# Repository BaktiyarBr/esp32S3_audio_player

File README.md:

# aka_walkman — ESP32-S3 Hi-Fi Audio Player

A portable, battery-powered hi-fi audio player built around the **ESP32-S3** and the
**Cirrus Logic CS43131** DAC/headphone amplifier, designed in **KiCad** on a custom PCB.
Firmware is planned with ESP-IDF / ESP-ADF and custom drivers.

## Features

- Stereo hi-fi playback to a 3.5 mm headphone jack (CS43131 DAC + integrated headphone amp, 24.576 MHz audio clock)
- Audio sources: microSD card, Bluetooth, (optionally) USB
- Single-cell (1S) Li-ion battery with USB-C charging and a fuel gauge
- Push-button power on/off with a hard power cut when off (LTC2954 controller)
- UI: Nokia 5110 LCD, rotary encoder with push switch, 4× Cherry MX keys + 2 tactile buttons
- USB-C with ESD protection and a CP2102N USB-UART bridge for flashing / debug

## Key components

| Function | Part |
|---|---|
| MCU | ESP32-S3-WROOM-2 (N32R16V: 32 MB flash / 16 MB PSRAM) |
| DAC / headphone amp | CS43131-CNZR |
| 1.8 V logic level translation (I²S / I²C) | TXU0204, PCA9306 |
| Battery charger | BQ25185 |
| Buck-boost 3.3 V rail | TPS63020 |
| 1.8 V LDOs (codec rails) | 3× LP5907MFX-1.8 |
| Fuel gauge | MAX17048G |
| Power on/off controller | LTC2954-1 |
| USB-UART | CP2102N |
| USB ESD | USBLC6-2SC6 |
| Display | Nokia 5110 (PCD8544) |
| Encoder | SIQ-02FVS3 |

Full BOM with LCSC part numbers: [`production/bom.csv`](production/bom.csv).

## Repository layout

```
aka_walkman.kicad_pro      KiCad project
aka_walkman.kicad_sch      Root schematic (MCU, USB, UI, SD card)
power.kicad_sch            Power sheet (charger, buck-boost, LDOs, fuel gauge, on/off)
Audio.kicad_sch            Audio sheet (CS43131, clock, level shifters)
aka_walkman.kicad_pcb      PCB layout
aka_walkman.kicad_dru      Custom design rules
libs/                      Project symbol / footprint / 3D libraries (easyeda)
datasheets/                Key datasheets
production/                Fabrication outputs (gerbers zip, BOM, CPL, IPC netlist)
```

## Opening the project

1. Open `aka_walkman.kicad_pro` in KiCad 9 or newer.
2. Project-local libraries are referenced from `libs/` via `sym-lib-table` / `fp-lib-table`.

## Manufacturing

Fabrication files in `production/` are generated with the KiCad *Fabrication Toolkit* plugin
(settings in `fabrication-toolkit-options.json`) for JLCPCB-style ordering.

## Status

Work in progress — hardware design stage.

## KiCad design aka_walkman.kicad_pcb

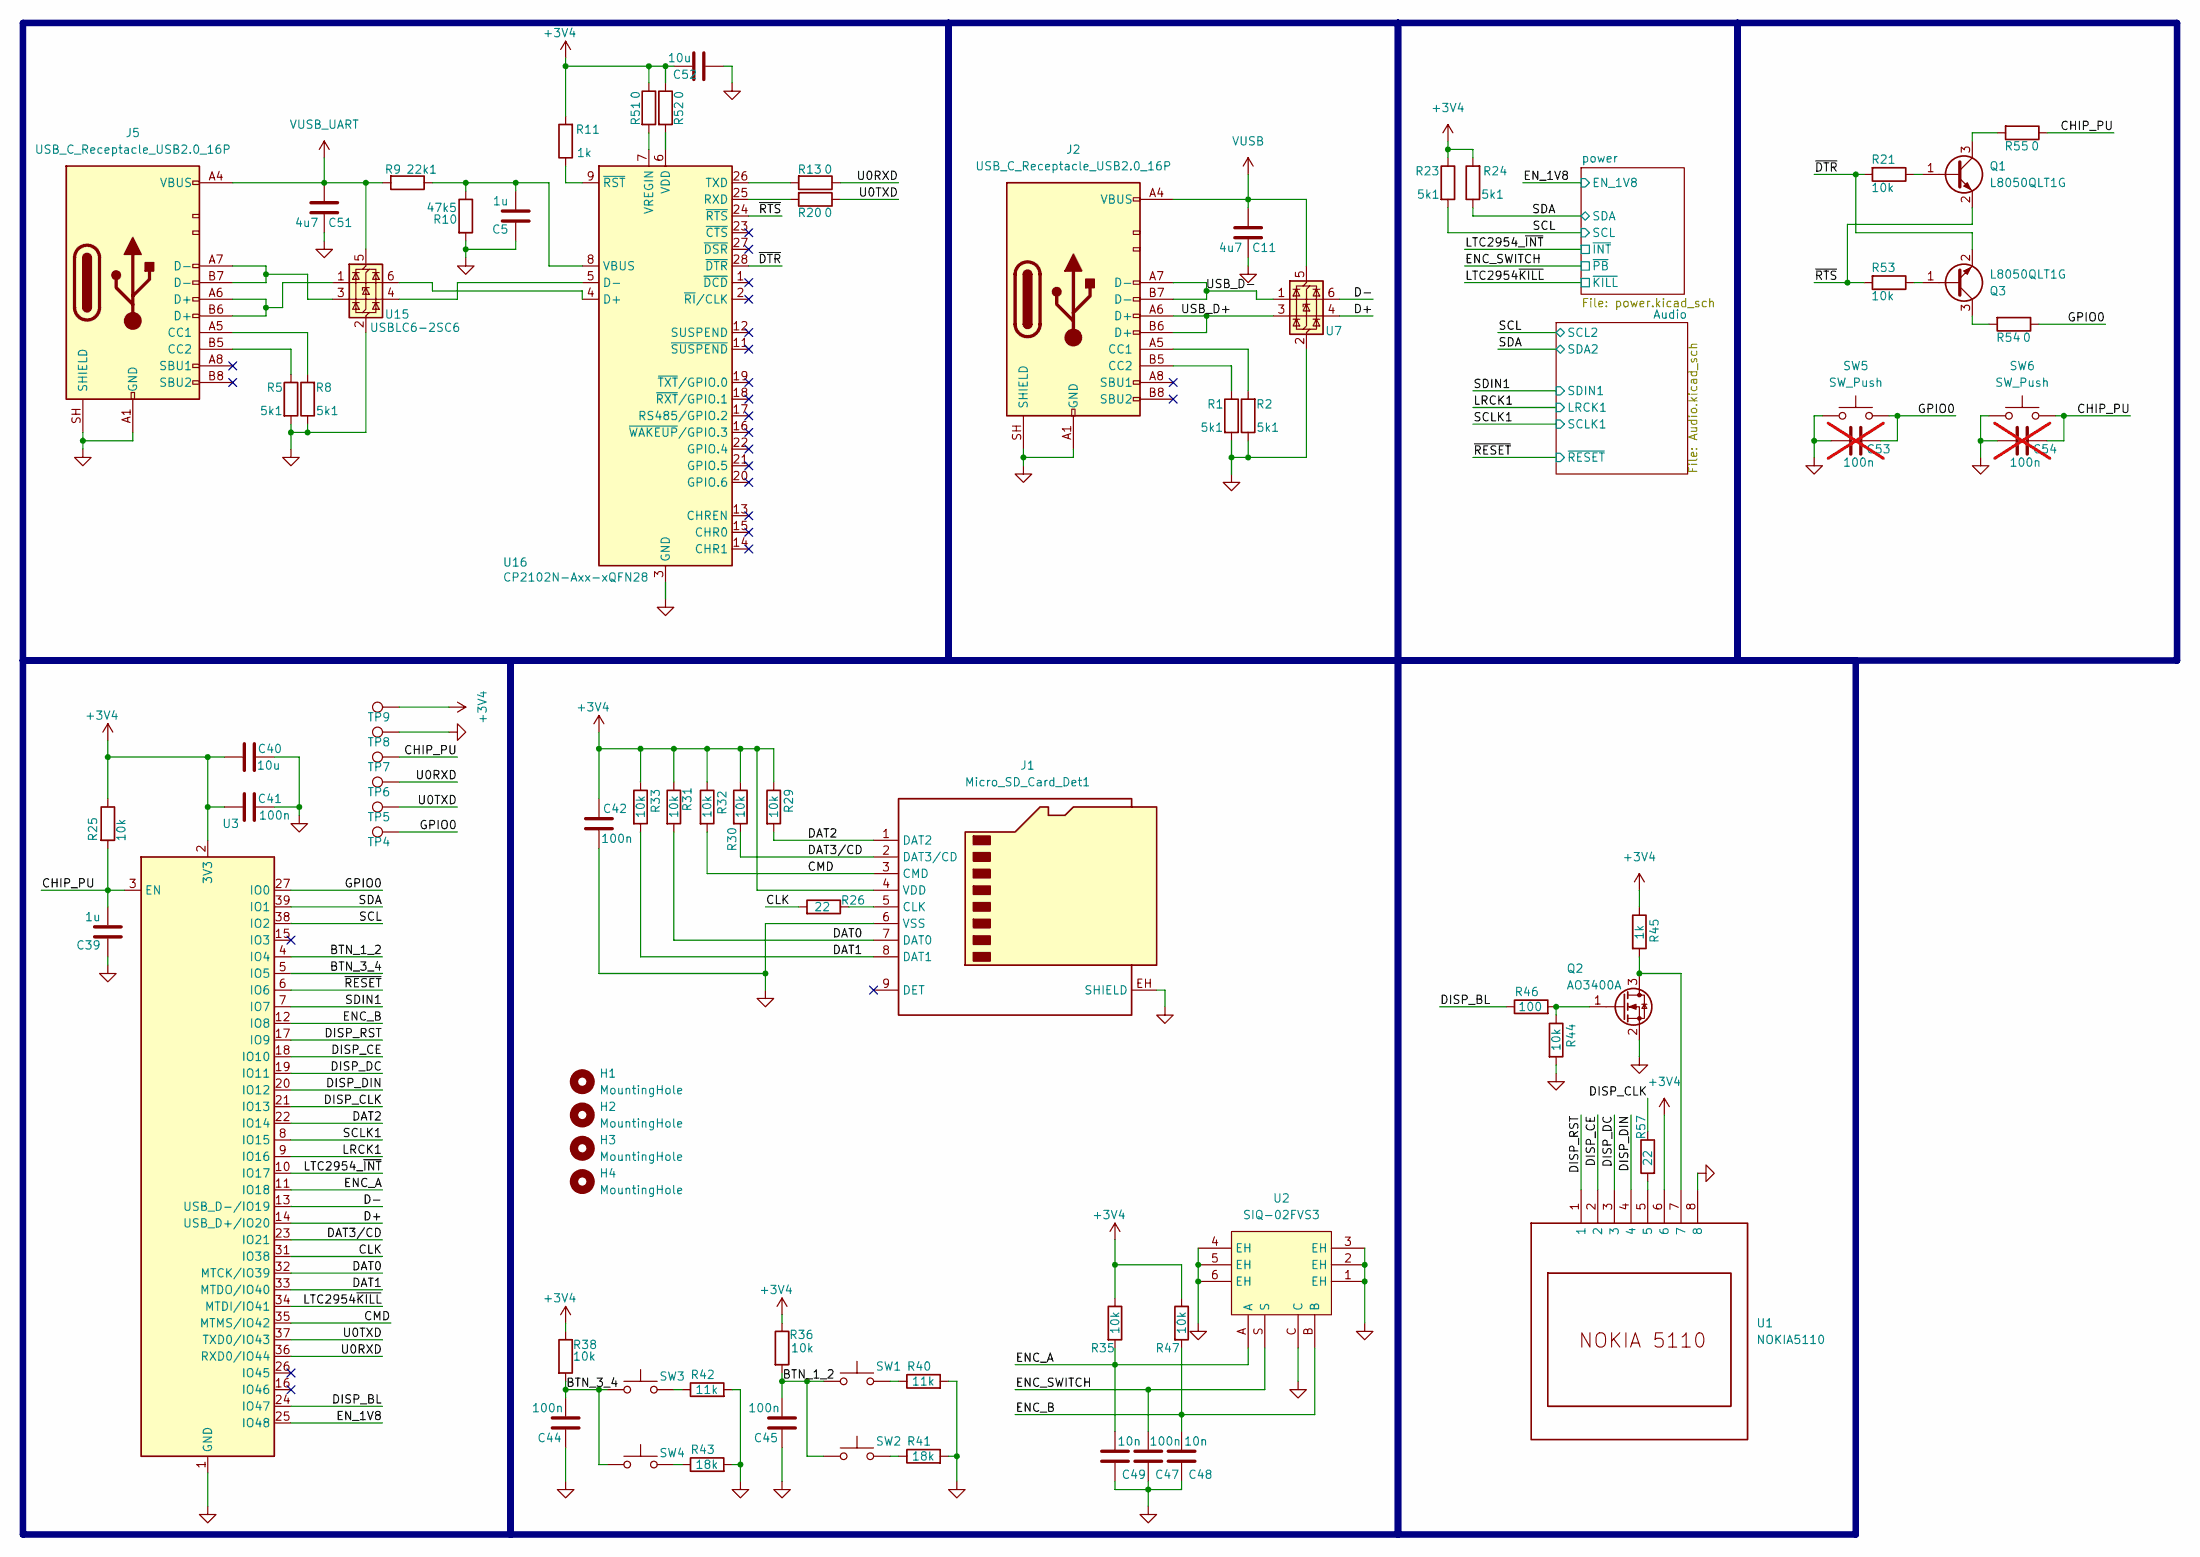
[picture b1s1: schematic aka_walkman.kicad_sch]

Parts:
C5, C39: 1u; C_0603_1608Metric; LCSC Part C15849
C11, C51: 4u7; C_0603_1608Metric; LCSC Part C1705
C40, C52: 10u; C_0603_1608Metric; LCSC Part C96446
C41, C42, C44, C45, C47: 100n; C_0603_1608Metric; LCSC Part C6119867
C48, C49: 10n; C_0603_1608Metric; LCSC Part C57112
C53, C54: 100n; C_0603_1608Metric; not fitted
H1, H2, H3, H4: MountingHole; MountingHole_2.7mm_M2.5
J1: Micro_SD_Card_Det1; SD-SMD_SD-47352-101; LCSC Part C293569
J2, J5: USB_C_Receptacle_USB2.0_16P; USB-TYPE-C-SMD_TYPE-C-16P-QTWT; LCSC Part C5187472
Q1, Q3: L8050QLT1G; SOT-23; LCSC Part C49581
Q2: AO3400A; SOT-23; LCSC Part C20917
R1, R2, R5, R8, R23, R24: 5k1; R_0603_1608Metric
R9: 22k1; R_0603_1608Metric
R10: 47k5; R_0603_1608Metric
R11, R45: 1k; R_0603_1608Metric
R13, R20, R51, R52, R54, R55: 0; R_0603_1608Metric
R21, R25, R29, R30, R31, R32, R33, R35, R36, R38, R44, R47, R53: 10k; R_0603_1608Metric
R26, R57: 22; R_0603_1608Metric; LCSC Part C26978
R40, R42: 11k; R_0603_1608Metric; LCSC Part C2906986
R41, R43: 18k; R_0603_1608Metric
R46: 100; R_0603_1608Metric; LCSC Part C22775
SW1, SW2, SW3, SW4: SW_Push; SW_Cherry_MX_PCB_1.00u
SW5, SW6: SW_Push; SW-SMD_L3.9-W3.0-P4.45
TP4, TP5, TP6, TP7, TP8, TP9: TestPoint; TestPoint_Pad_D1.5mm
U1: NOKIA5110; NOKIA5110-M01
U2: SIQ-02FVS3; SW-SMD_SIQ-02FVS3_1; MPN SIQ-02FVS3; LCSC Part C2925423
U3: ESP32-S3-WROOM-2; LCSC Part C42417293
U7, U15: USBLC6-2SC6; SOT-23-6; LCSC Part C7519
U16: CP2102N-Axx-xQFN28; QFN-28-1EP_5x5mm_P0.5mm_EP3.35x3.35mm; LCSC Part C964632

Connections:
+3V4: C40.1, C41.1, C42.1, C52.2, J1.4 (VDD), R11.2, R23.1, R24.2, R25.1, R29.1, R30.1, R31.1, R32.1, R33.1, R35.1, R36.1, R38.1, R45.1, R47.1, R51.1, R52.1, TP9.1 (1_1), U1.6, U3.2 (3V3); also elsewhere on the board
/BTN_1_2: C45.2, R36.2, SW1.1, SW2.1, U3.4 (IO4)
/BTN_3_4: C44.2, R38.2, SW3.1, SW4.1, U3.5 (IO5)
/CHIP_PU: C39.2, C54.1, R25.2, R55.1, SW6.2, TP7.1 (1_1), U3.3 (EN)
/CLK: R26.2, U3.31 (IO38)
/CMD: J1.3 (CMD), R32.2, U3.35 (MTMS/IO42)
/D+: U3.14 (USB_D+/IO20), U7.4 (I/O2)
/D-: U3.13 (USB_D-/IO19), U7.6 (I/O1)
/DAT0: J1.7 (DAT0), R31.2, U3.32 (MTCK/IO39)
/DAT1: J1.8 (DAT1), R33.2, U3.33 (MTDO/IO40)
/DAT2: J1.1 (DAT2), R29.2, U3.22 (IO14)
/DAT3/CD: J1.2 (DAT3/CD), R30.2, U3.23 (IO21)
/DISP_BL: R46.1, U3.24 (IO47)
/DISP_CE: U1.2, U3.18 (IO10)
/DISP_CLK: R57.1, U3.21 (IO13)
/DISP_DC: U1.3, U3.19 (IO11)
/DISP_DIN: U1.4, U3.20 (IO12)
/DISP_RST: U1.1, U3.17 (IO9)
/ENC_A: C49.2, R35.2, U2.A, U3.11 (IO18)
/ENC_B: C48.2, R47.2, U2.B, U3.12 (IO8)
/ENC_SWITCH: C47.2, U2.S; also elsewhere on the board
/EN_1V8: U3.25 (IO48); also elsewhere on the board
/GPIO0: C53.1, R54.1, SW5.2, TP4.1 (1_1), U3.27 (IO0)
/LRCK1: U3.9 (IO16); also elsewhere on the board
/LTC2954_~INT: U3.10 (IO17); also elsewhere on the board
/LTC2954~KILL: U3.34 (MTDI/IO41); also elsewhere on the board
/SCL: R23.2, U3.38 (IO2); also elsewhere on the board
/SCLK1: U3.8 (IO15); also elsewhere on the board
/SDA: R24.1, U3.39 (IO1); also elsewhere on the board
/SDIN1: U3.7 (IO7); also elsewhere on the board
/U0RXD: R13.1, TP6.1 (1_1), U3.36 (RXD0/IO44)
/U0TXD: R20.1, TP5.1 (1_1), U3.37 (TXD0/IO43)
/USB_D+: J2.A6 (D+), J2.B6 (D+), U7.3 (I/O2)
/USB_D-: J2.A7 (D-), J2.B7 (D-), U7.1 (I/O1)
/~DTR: Q3.2 (E), R21.2, U16.28 (~DTR)
/~RESET: U3.6 (IO6); also elsewhere on the board
/~RTS: Q1.2 (E), R53.2, U16.24 (~RTS)
GND: C5.1, C11.2, C39.1, C40.2, C41.2, C42.2, C44.1, C45.1, C47.1, C48.1, C49.1, C51.2, C52.1, C53.2, C54.2, J1.6 (VSS), J1.EH (SHIELD), J2.A1 (GND), J2.A12 (GND), J2.B1 (GND), J2.B12 (GND), J2.SH (SHIELD), J5.A1 (GND), J5.A12 (GND), J5.B1 (GND), J5.B12 (GND), J5.SH (SHIELD), Q2.2 (S), R1.2, R2.1, R5.2, R8.1, R10.2, R40.2, R41.2, R42.2, R43.2, R44.2, SW5.1, SW6.1, TP8.1 (1_1), U1.8, U2.1 (EH), U2.2 (EH), U2.3 (EH), U2.4 (EH), U2.5 (EH), U2.6 (EH), U2.C, U3.1 (GND), U3.40 (GND), U3.41 (GND), U7.2 (GND), U15.2 (GND), U16.3 (GND), U16.29 (GND); also elsewhere on the board
unnamed: J1.5 (CLK), R26.1
unnamed: J2.A5 (CC1), R2.2
unnamed: J2.B5 (CC2), R1.1
unnamed: J5.A5 (CC1), R8.2
unnamed: J5.B5 (CC2), R5.1
unnamed: J5.A6 (D+), J5.B6 (D+), U15.1 (I/O1)
unnamed: J5.A7 (D-), J5.B7 (D-), U15.3 (I/O2)
unnamed: Q1.1 (B), R21.1
unnamed: Q1.3 (C), R55.2
unnamed: Q2.3 (D), R45.2, U1.7
unnamed: Q2.1 (G), R44.1, R46.2
unnamed: Q3.1 (B), R53.1
unnamed: Q3.3 (C), R54.2
unnamed: R40.1, SW1.2
unnamed: R41.1, SW2.2
unnamed: R42.1, SW3.2
unnamed: R43.1, SW4.2
unnamed: R57.2, U1.5
unnamed: U15.6 (I/O1), U16.4 (D+)
unnamed: U15.4 (I/O2), U16.5 (D-)
unnamed: R20.2, U16.25 (RXD)
unnamed: R13.2, U16.26 (TXD)
unnamed: C5.2, R9.1, R10.1, U16.8 (VBUS)
unnamed: R52.2, U16.6 (VDD)
unnamed: R51.2, U16.7 (VREGIN)
unnamed: R11.1, U16.9 (~RST)
VUSB: C11.1, J2.A4 (VBUS), J2.A9 (VBUS), J2.B4 (VBUS), J2.B9 (VBUS), U7.5 (VBUS); also elsewhere on the board
VUSB_UART: C51.1, J5.A4 (VBUS), J5.A9 (VBUS), J5.B4 (VBUS), J5.B9 (VBUS), R9.2, U15.5 (VBUS); also elsewhere on the board

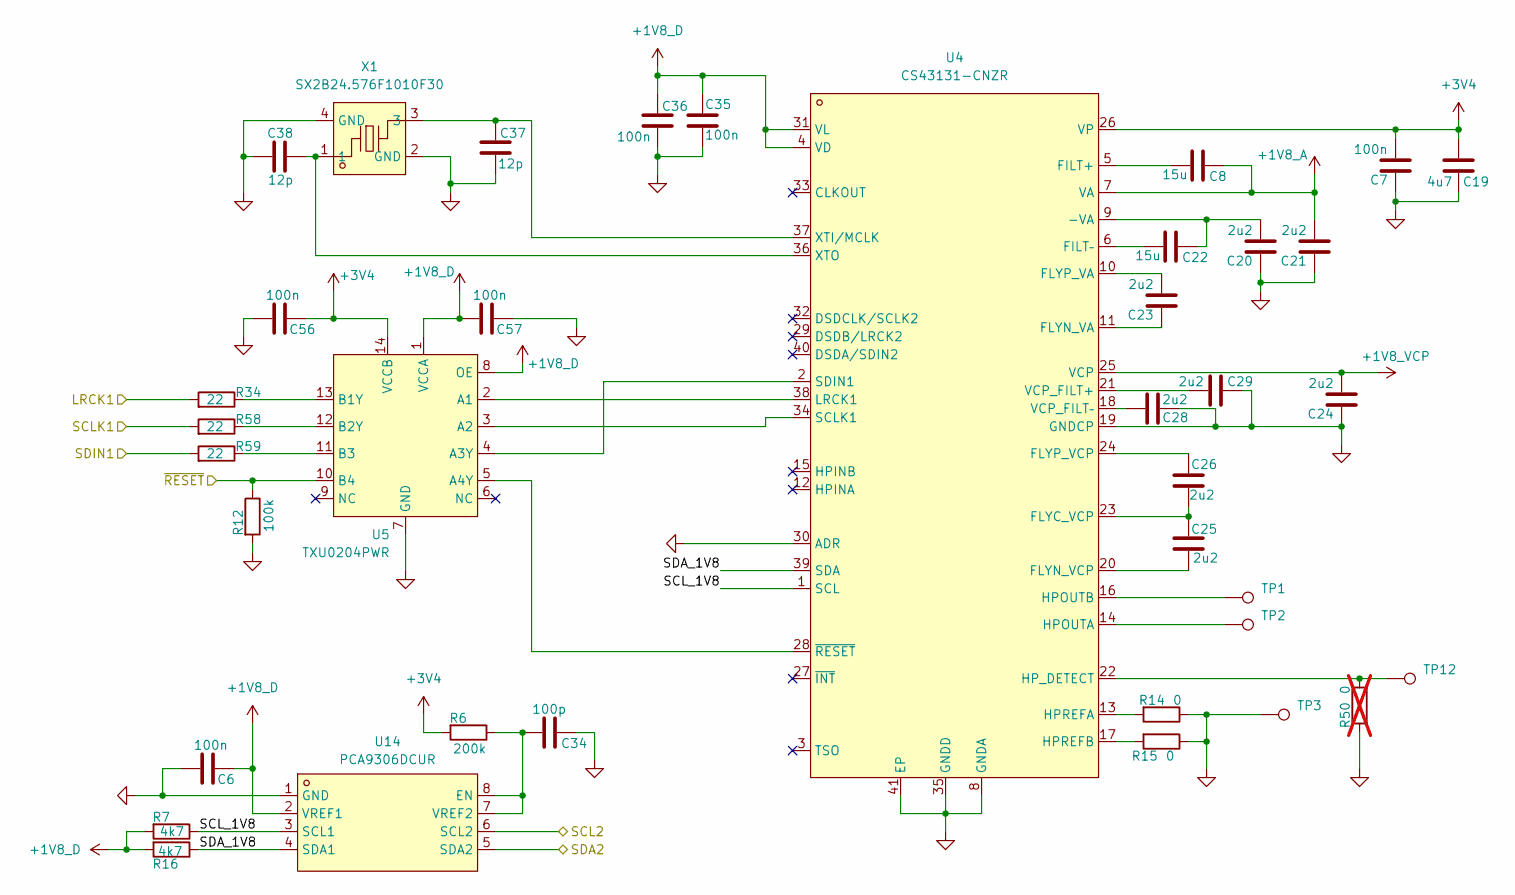
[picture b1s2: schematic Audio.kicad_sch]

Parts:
C6, C7, C35, C36, C56, C57: 100n; C_0603_1608Metric; LCSC Part C6119867
C8, C22: 15u; C_0805_2012Metric; LCSC Part C5367448
C19: 4u7; C_0603_1608Metric; LCSC Part C1705
C20, C21, C23, C24, C25, C26, C28, C29: 2u2; C_0603_1608Metric; LCSC Part C57895
C34: 100p; C_0603_1608Metric; LCSC Part C14665
C37, C38: 12p; C_0402_1005Metric; LCSC Part C26406
R6: 200k; R_0402_1005Metric; LCSC Part C2906866
R7, R16: 4k7; R_0603_1608Metric
R12: 100k; R_0603_1608Metric; LCSC Part C95177
R14, R15: 0; R_0603_1608Metric
R34, R58, R59: 22; R_0603_1608Metric; LCSC Part C26978
R50: 0; R_0603_1608Metric; not fitted
TP1, TP2, TP3, TP12: TestPoint; TestPoint_Pad_1.0x1.0mm
U4: CS43131-CNZR; TQFN-40_L5.0-W5.0-P0.40-TL-EP3.5; MPN CS43131-CNZR; LCSC Part C965907
U5: TXU0204PWR; TSSOP-14_L5.0-W4.4-P0.65-LS6.4-BL; MPN TXU0204PWR; LCSC Part C4363888
U14: PCA9306DCUR; SSOP-8_L2.0-W2.3-P0.50-LS3.1-BR; MPN PCA9306DCUR; LCSC Part C33196
X1: SX2B24.576F1010F30; CRYSTAL-SMD_4P-L2.5-W2.0-BL; MPN SX2B24.576F1010F30; LCSC Part C7301978

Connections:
+1V8_A: C8.1, C21.2, U4.7 (VA); also elsewhere on the board
+1V8_D: C6.1, C35.1, C36.1, C57.2, R7.2, R16.2, U4.4 (VD), U4.31 (VL), U5.1 (VCCA), U5.8 (OE), U14.2 (VREF1); also elsewhere on the board
+1V8_VCP: C24.2, U4.25 (VCP); also elsewhere on the board
+3V4: C7.2, C19.1, C56.1, R6.2, U4.26 (VP), U5.14 (VCCB); also elsewhere on the board
/Audio/SCL_1V8: R7.1, U4.1 (SCL), U14.3 (SCL1)
/Audio/SDA_1V8: R16.1, U4.39 (SDA), U14.4 (SDA1)
/LRCK1: R34.2; also elsewhere on the board
/SCL: U14.6 (SCL2); also elsewhere on the board
/SCLK1: R58.2; also elsewhere on the board
/SDA: U14.5 (SDA2); also elsewhere on the board
/SDIN1: R59.2; also elsewhere on the board
/~RESET: R12.1, U5.10 (B4); also elsewhere on the board
GND: C6.2, C7.1, C19.2, C20.1, C21.1, C24.1, C28.1, C29.1, C34.1, C35.2, C36.2, C37.2, C38.1, C56.2, C57.1, R12.2, R14.1, R15.1, R50.2, TP3.1 (1_1), U4.8 (GNDA), U4.19 (GNDCP), U4.30 (ADR), U4.35 (GNDD), U4.41 (EP), U5.7 (GND), U14.1 (GND), X1.2 (GND), X1.4 (GND); also elsewhere on the board
unnamed: C20.2, C22.1, U4.9 (-VA)
unnamed: C8.2, U4.5 (FILT+)
unnamed: C22.2, U4.6 (FILT–)
unnamed: C25.1, C26.2, U4.23 (FLYC_VCP)
unnamed: C23.1, U4.11 (FLYN_VA)
unnamed: C25.2, U4.20 (FLYN_VCP)
unnamed: C23.2, U4.10 (FLYP_VA)
unnamed: C26.1, U4.24 (FLYP_VCP)
unnamed: TP2.1 (1_1), U4.14 (HPOUTA)
unnamed: TP1.1 (1_1), U4.16 (HPOUTB)
unnamed: R14.2, U4.13 (HPREFA)
unnamed: R15.2, U4.17 (HPREFB)
unnamed: R50.1, TP12.1 (1_1), U4.22 (HP_DETECT)
unnamed: U4.38 (LRCK1), U5.2 (A1)
unnamed: U4.34 (SCLK1), U5.3 (A2)
unnamed: U4.2 (SDIN1), U5.4 (A3Y)
unnamed: C29.2, U4.21 (VCP_FILT+)
unnamed: C28.2, U4.18 (VCP_FILT–)
unnamed: C37.1, U4.37 (XTI/MCLK), X1.3
unnamed: C38.2, U4.36 (XTO), X1.1
unnamed: U4.28 (~RESET), U5.5 (A4Y)
unnamed: R34.1, U5.13 (B1Y)
unnamed: R58.1, U5.12 (B2Y)
unnamed: R59.1, U5.11 (B3)
unnamed: C34.2, R6.1, U14.7 (VREF2), U14.8 (EN)

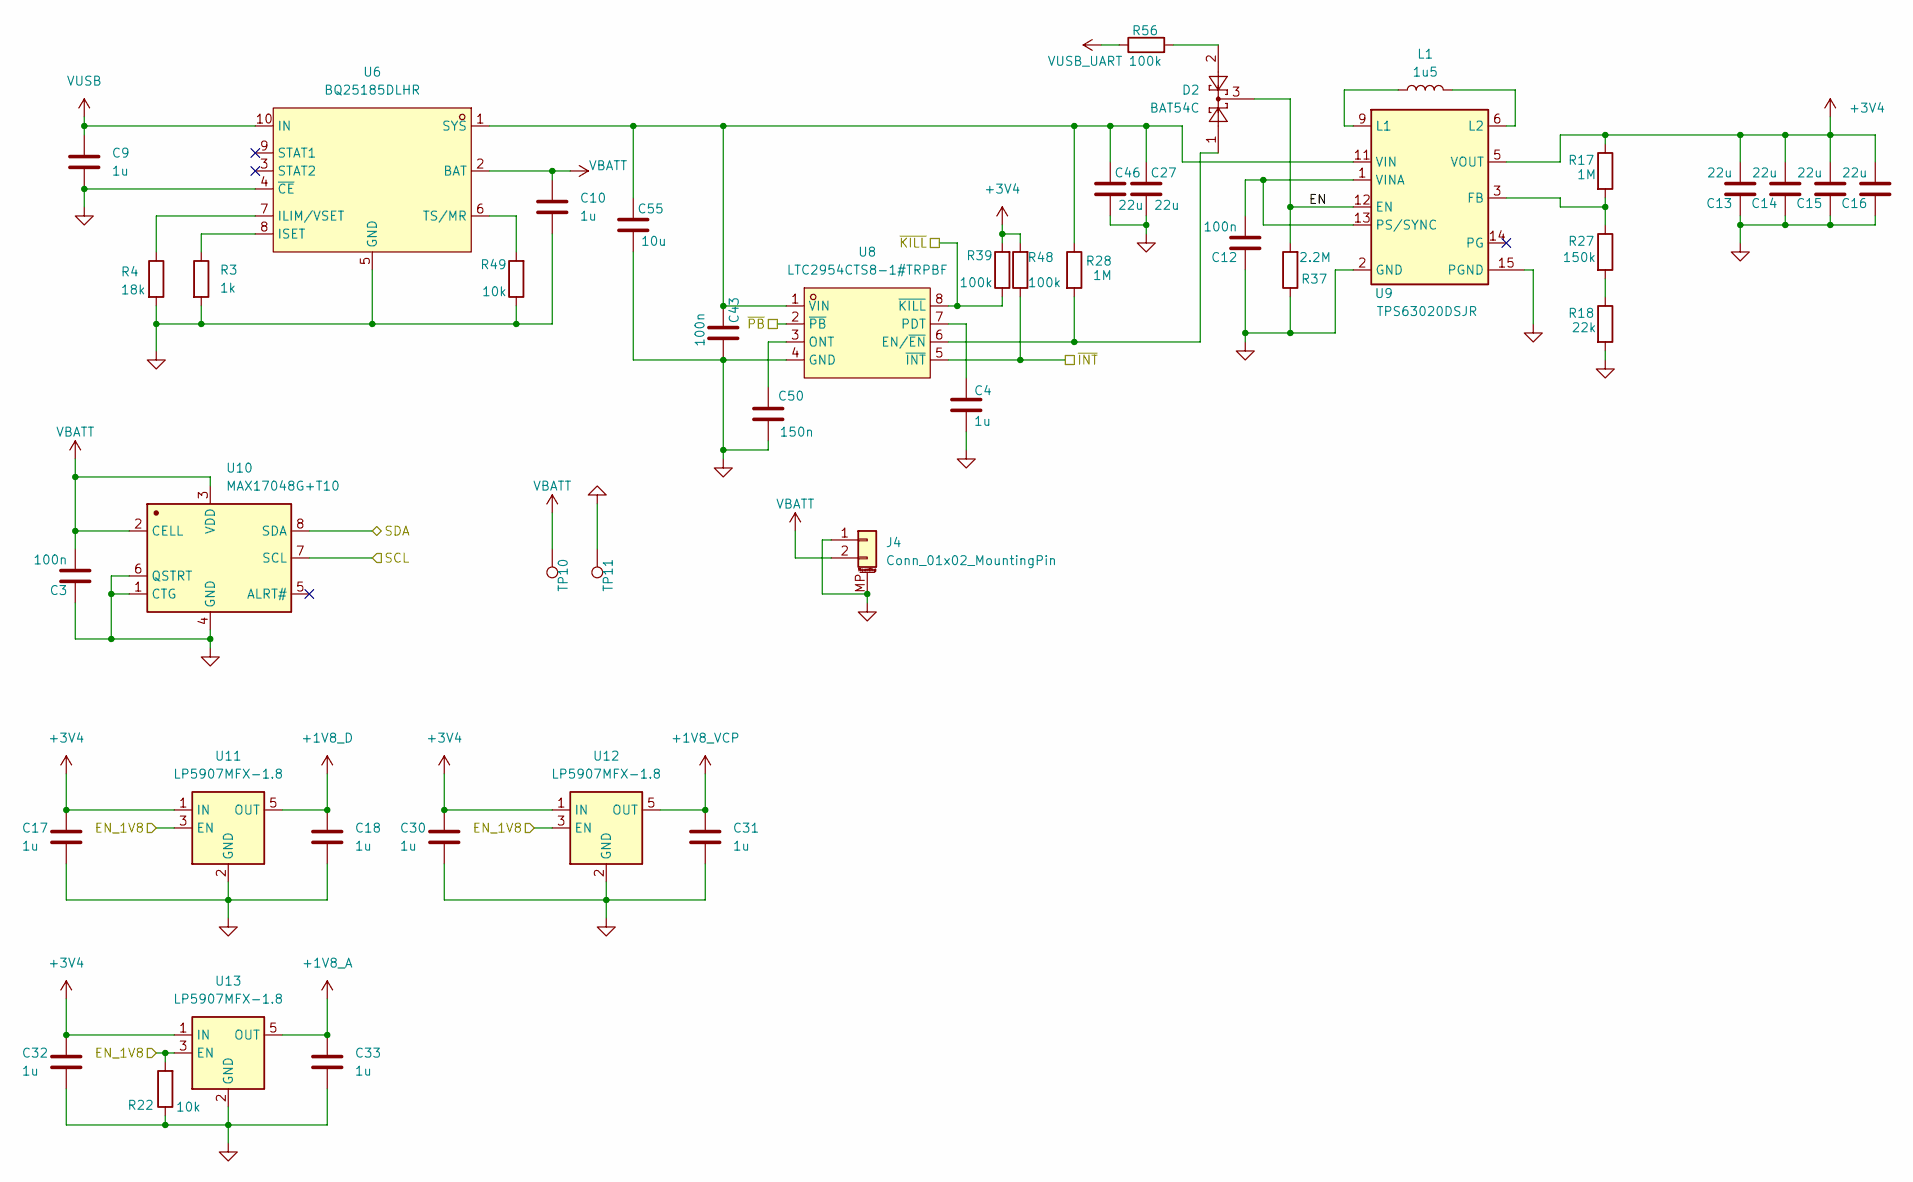
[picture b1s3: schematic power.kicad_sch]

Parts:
C3, C12, C43: 100n; C_0603_1608Metric; LCSC Part C6119867
C4: 1u; C_0603_1608Metric; LCSC Part C15849
C9, C10, C17, C18, C30, C31, C32, C33: 1u; C_0603_1608Metric; Part-DB Footprint 0603; LCSC Part C15849
C13, C14, C15, C16, C27, C46: 22u; C_0805_2012Metric; LCSC Part C45783
C50: 150n; C_0603_1608Metric; Part-DB Footprint 0603; LCSC Part C513735
C55: 10u; C_0603_1608Metric; LCSC Part C96446
D2: BAT54C; SOT-23; LCSC Part C916424
J4: Conn_01x02_MountingPin; JST_GH_SM02B-GHS-TB_1x02-1MP_P1.25mm_Horizontal
L1: 1u5; L_Bourns-SRN4018; LCSC Part C5349662
R3: 1k; R_0603_1608Metric
R4: 18k; R_0603_1608Metric
R17, R28: 1M; R_0603_1608Metric
R18: 22k; R_0603_1608Metric
R22, R49: 10k; R_0603_1608Metric
R27: 150k; R_0603_1608Metric
R37: 2.2M; R_0603_1608Metric; LCSC Part C2933170
R39, R48, R56: 100k; R_0603_1608Metric; LCSC Part C95177
TP10, TP11: TestPoint; TestPoint_Pad_D1.5mm
U6: BQ25185DLHR; WSON-10_L2.2-W2.0-P0.40-BL-EP_TI_DLH0010A; MPN BQ25185DLHR; LCSC Part C19725033
U8: LTC2954CTS8-1#TRPBF; TSOT-23-8_L2.9-W1.6-P0.65-LS2.8-BL; MPN LTC2954CTS8-1#TRPBF; LCSC Part C683782
U9: TPS63020DSJR; VSON-14_L4.0-W3.0-P0.50-BL-EP_TI_DSJ; Manufacturer Part TPS63020DSJR; LCSC Part C15483
U10: MAX17048G+T10; TDFN-8_L2.0-W2.0-P0.50-BL-EP1.2; Manufacturer Part MAX17048G+T10; LCSC Part C2682616
U11, U12, U13: LP5907MFX-1.8; SOT-23-5; LCSC Part C92498

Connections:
+1V8_A: C33.1, U13.5 (OUT); also elsewhere on the board
+1V8_D: C18.1, U11.5 (OUT); also elsewhere on the board
+1V8_VCP: C31.1, U12.5 (OUT); also elsewhere on the board
+3V4: C13.2, C14.2, C15.2, C16.2, C17.1, C30.1, C32.1, R17.1, R39.2, R48.2, U9.4 (VOUT), U9.5 (VOUT), U11.1 (IN), U12.1 (IN), U13.1 (IN); also elsewhere on the board
/ENC_SWITCH: U8.2 (~PB); also elsewhere on the board
/EN_1V8: R22.2, U11.3 (EN), U12.3 (EN), U13.3 (EN); also elsewhere on the board
/LTC2954_~INT: R48.1, U8.5 (~INT); also elsewhere on the board
/LTC2954~KILL: R39.1, U8.8 (~KILL); also elsewhere on the board
/SCL: U10.7 (SCL); also elsewhere on the board
/SDA: U10.8 (SDA); also elsewhere on the board
/power/EN: D2.3, R37.2, U9.12 (EN)
GND: C3.1, C4.2, C9.2, C10.2, C12.1, C13.1, C14.1, C15.1, C16.1, C17.2, C18.2, C27.2, C30.2, C31.2, C32.2, C33.2, C43.2, C46.2, C50.2, C55.2, J4.1, J4.MP (MountPin), R3.2, R4.2, R18.2, R22.1, R37.1, R49.1, TP11.1 (1_1), U6.4 (~CE), U6.5 (GND), U6.11 (EP), U8.4 (GND), U9.2 (GND), U9.15 (PGND), U10.1 (CTG), U10.4 (GND), U10.6 (QSTRT), U10.9 (EP), U11.2 (GND), U12.2 (GND), U13.2 (GND); also elsewhere on the board
unnamed: D2.2, R56.2
unnamed: L1.1, U9.8 (L1), U9.9 (L1)
unnamed: L1.2, U9.6 (L2), U9.7 (L2)
unnamed: R18.1, R27.2
unnamed: R4.1, U6.7 (ILIM/VSET)
unnamed: R3.1, U6.8 (ISET)
unnamed: C27.1, C43.1, C46.1, C55.1, R28.1, U6.1 (SYS), U8.1 (VIN), U9.10 (VIN), U9.11 (VIN)
unnamed: R49.2, U6.6 (TS/MR)
unnamed: D2.1, R28.2, U8.6 (EN/~EN)
unnamed: C50.1, U8.3 (ONT)
unnamed: C4.1, U8.7 (PDT)
unnamed: R17.2, R27.1, U9.3 (FB)
unnamed: C12.2, U9.1 (VINA), U9.13 (PS/SYNC)
VBATT: C3.2, C10.1, J4.2, TP10.1 (1_1), U6.2 (BAT), U10.2 (CELL), U10.3 (VDD)
VUSB: C9.1, U6.10 (IN); also elsewhere on the board
VUSB_UART: R56.1; also elsewhere on the board

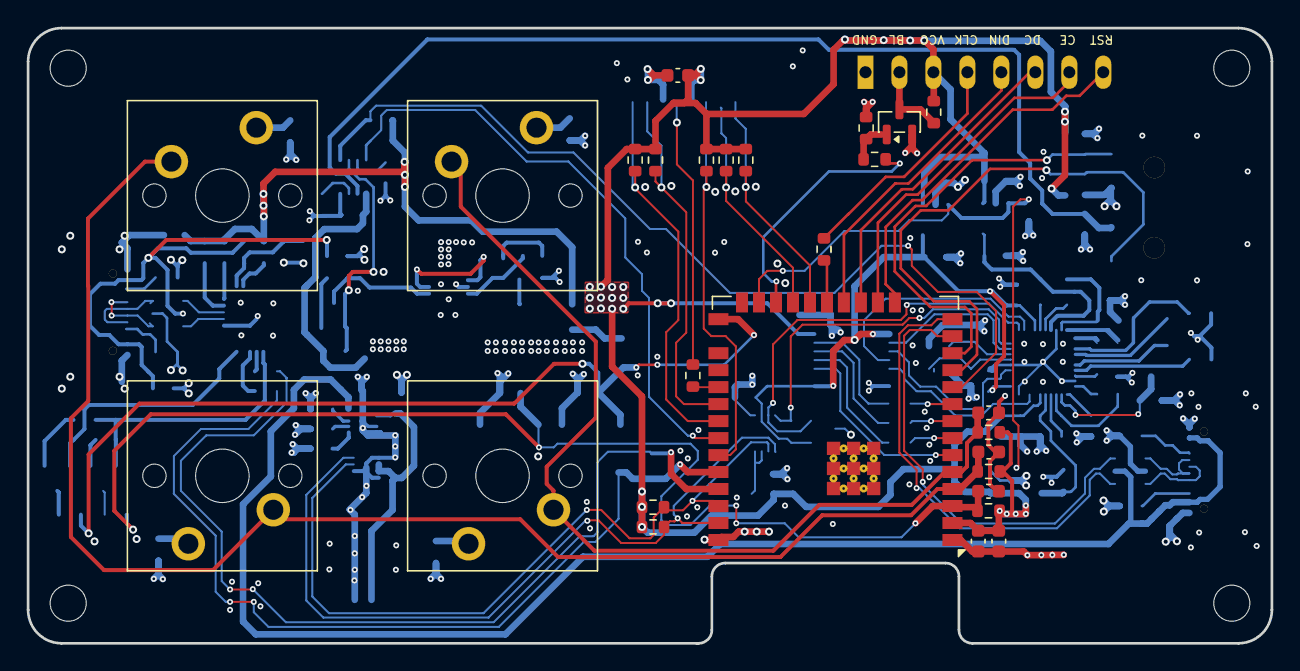
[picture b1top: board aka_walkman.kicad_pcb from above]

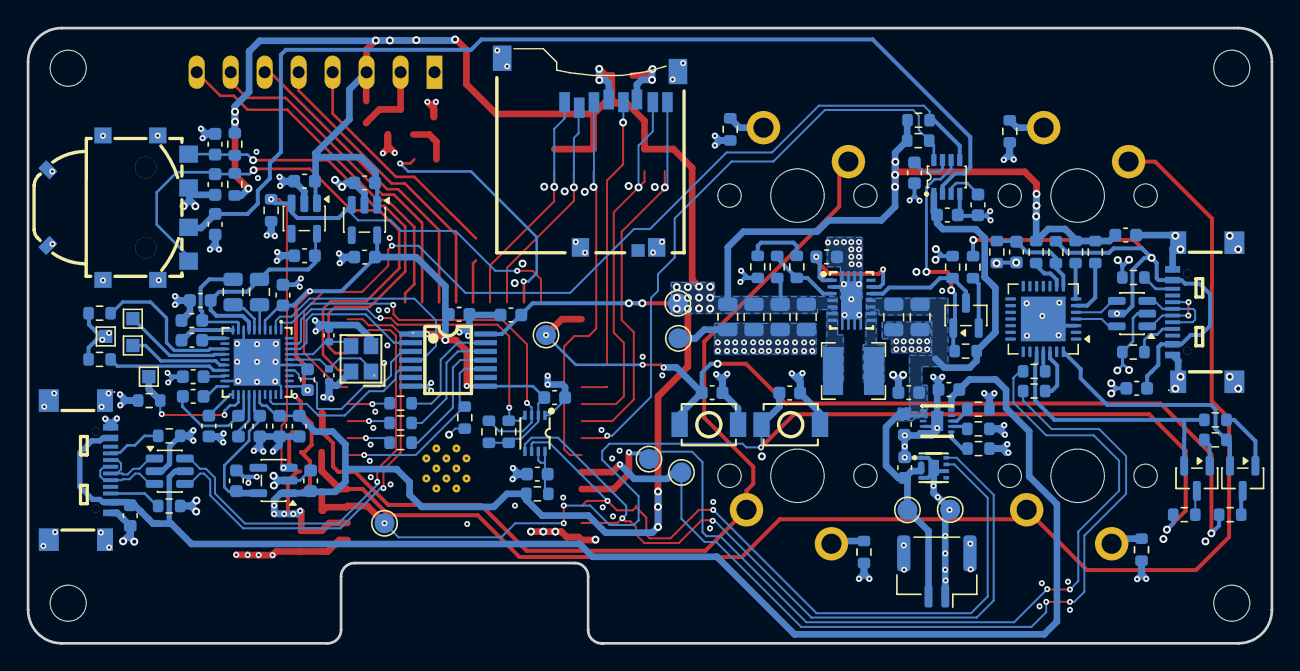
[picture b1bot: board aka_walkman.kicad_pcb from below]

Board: 4 copper layers, 93.0 x 46.0 mm, 161 parts (129 on the bottom side), 111 nets.

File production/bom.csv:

Designator,Footprint,Quantity,Value,LCSC Part #
"C10, C17, C18, C30, C31, C32, C33, C9",0603,8,1u,C15849
"C13, C14, C15, C16, C27, C46",0805,6,22u, C45783
"C22, C8",0805,2,15u,C5367448
"C37, C38",0402,2,12p,
"C40, C52, C55",0603,3,10u,
C43,0603,1,100n,C15849
"C48, C49",0603,2,10n,
C50,0603,1,150n,C15849
"C53, C54",0603,2,100n,
D2,SOT-23,1,BAT54C,
J1,SD-SMD_SD-47352-101,1,Micro_SD_Card_Det1,
"J2, J5",USB-TYPE-C-SMD_TYPE-C-16P-QTWT,2,USB_C_Receptacle_USB2.0_16P,
J4,JST_GH_SM02B-GHS-TB_1x02-1MP_P1.25mm_Horizontal,1,Conn_01x02_MountingPin,
L1,L_Bourns-SRN4018,1,1u5,C5349662
"Q1, Q3",SOT-23,2,L8050QLT1G,C49581
Q2,SOT-23,1,AO3400A,
"R1, R2, R23, R24, R5, R8",0603,6,5k1,
R10,0603,1,47k5,
"R11, R3, R45",0603,3,1k,
"R12, R39, R48, R56",0603,4,100k,
"R13, R14, R15, R20, R50, R51, R52, R54, R55",0603,9,0,
"R16, R7",0603,2,4k7,
"R17, R28",0603,2,1M,
R18,0603,1,22k,
"R21, R22, R25, R29, R30, R31, R32, R33, R35, R36, R38, R44, R47, R49, R53",0603,15,10k,
"R26, R34, R57, R58, R59",0603,5,22,C26978
R27,0603,1,150k,
R37,0603,1,2.2M,
"R4, R41, R43",0603,3,18k,
"R40, R42",0603,2,11k,C60490
R46,0603,1,100,C60490
R6,0603,1,200k,
R9,0603,1,22k1,
"SW1, SW2, SW3, SW4",SW_Cherry_MX_PCB_1.00u,4,SW_Push,
"SW5, SW6",SW-SMD_L3.9-W3.0-P4.45,2,SW_Push,
U1,NOKIA5110-M01,1,NOKIA5110,
U10,TDFN-8_L2.0-W2.0-P0.50-BL-EP1.2,1,MAX17048G+T10,C2682616
"U11, U12, U13",SOT-23-5,3,LP5907MFX-1.8,C92498
U14,SSOP-8_L2.0-W2.3-P0.50-LS3.1-BR,1,PCA9306DCUR,C33196
"U15, U7",SOT-23-6,2,USBLC6-2SC6,C7519
U16,QFN-28-1EP_5x5mm_P0.5mm_EP3.35x3.35mm,1,CP2102N-Axx-xQFN28,C964632
U2,SW-SMD_SIQ-02FVS3_1,1,SIQ-02FVS3,C2925423
U3,ESP32-S3-WROOM-2,1,ESP32-S3-WROOM-2,C42417293
U4,TQFN-40_L5.0-W5.0-P0.40-TL-EP3.5,1,CS43131-CNZR,C965907
U5,TSSOP-14_L5.0-W4.4-P0.65-LS6.4-BL,1,TXU0204PWR,C4363888
U6,WSON-10_L2.2-W2.0-P0.40-BL-EP_TI_DLH0010A,1,BQ25185DLHR,C19725033
U8,TSOT-23-8_L2.9-W1.6-P0.65-LS2.8-BL,1,LTC2954CTS8-1#TRPBF,C683782
U9,VSON-14_L4.0-W3.0-P0.50-BL-EP_TI_DSJ,1,TPS63020DSJR,C15483
X1,CRYSTAL-SMD_4P-L2.5-W2.0-BL,1,SX2B24.576F1010F30,C7301978
